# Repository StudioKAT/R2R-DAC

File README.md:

# R2R DAC

## 概要 / Overview

**R2R DAC** は、5つのゲート信号を階段状のコントロール電圧（CV）に変換する、2HPサイズのR-2RラダーDACモジュールです。
5つのゲート入力（/2, /4, /8, /16, /32）のON/OFFの組み合わせによって、0〜31段階のステップ電圧を生成する5ビットのデジタル→アナログ変換器として動作します。

クロックディバイダーやゲートシーケンサーと組み合わせることで、周期的な階段波、疑似ランダムなCVパターン、アルペジオ風のピッチ変化、フィルターやVCAのステップモジュレーションなどを簡単に作ることができます。
CV出力にはアッテネーターを備えており、ピッチCVからモジュレーション用途まで、パッチに合わせて出力レベルを調整できます。

**Update:** v2.0では、v1.0の4ビット仕様から5ビット仕様へ変更され、生成できるステップ数が16段階から32段階に拡張されました。

**R2R DAC** is a compact 2HP R-2R ladder DAC module that converts five gate signals into stepped control voltages (CV).
By combining the ON/OFF states of the five gate inputs (/2, /4, /8, /16, /32), it functions as a 5-bit digital-to-analog converter capable of generating 32 discrete voltage steps (0–31).

When paired with clock dividers or gate sequencers, it can create stepped waveforms, pseudo-random CV patterns, arpeggio-like pitch movement, or stepped modulation for filters, VCAs, and other CV destinations.
The CV output is equipped with an attenuator, allowing the output level to be adjusted for anything from pitch control to general modulation use.

**Update:** In v2.0, the design has been updated from the 4-bit configuration of v1.0 to a 5-bit R-2R DAC, expanding the available resolution from 16 steps to 32 steps.

## 仕様 / Spec
- Format: Eurorack
- Function: R2R DAC
- Current needs: +12V: 15mA, -12V: 15mA
- Width: 2 HP
- Depth: 28mm (including power connector)

## 販売 / Sales

StudioKATオフィシャルショップで販売しています。(日本国内限定)  
https://www.studiokat.jp/items/149564763

## ライセンス / License

この作品は [Creative Commons 表示 - 継承 4.0 国際 (CC BY-SA 4.0)](https://creativecommons.org/licenses/by-sa/4.0/deed.ja) の下でライセンスされています。  
This work is licensed under the [Creative Commons Attribution-ShareAlike 4.0 International License](https://creativecommons.org/licenses/by-sa/4.0/).

## クレジット / Credits

- Designed by : StudioKAT
- Website : https://www.studiokat.jp/
- GitHub : https://github.com/StudioKAT
- X(Twitter) : https://x.com/StudioKAT_synth
- Instagram : https://www.instagram.com/studiokat_modular/

## 更新履歴 / Changelog

- `2025-11-22` v1.0 Released version 1.0
- `2026-07-05` v2.0 Released version 2.0

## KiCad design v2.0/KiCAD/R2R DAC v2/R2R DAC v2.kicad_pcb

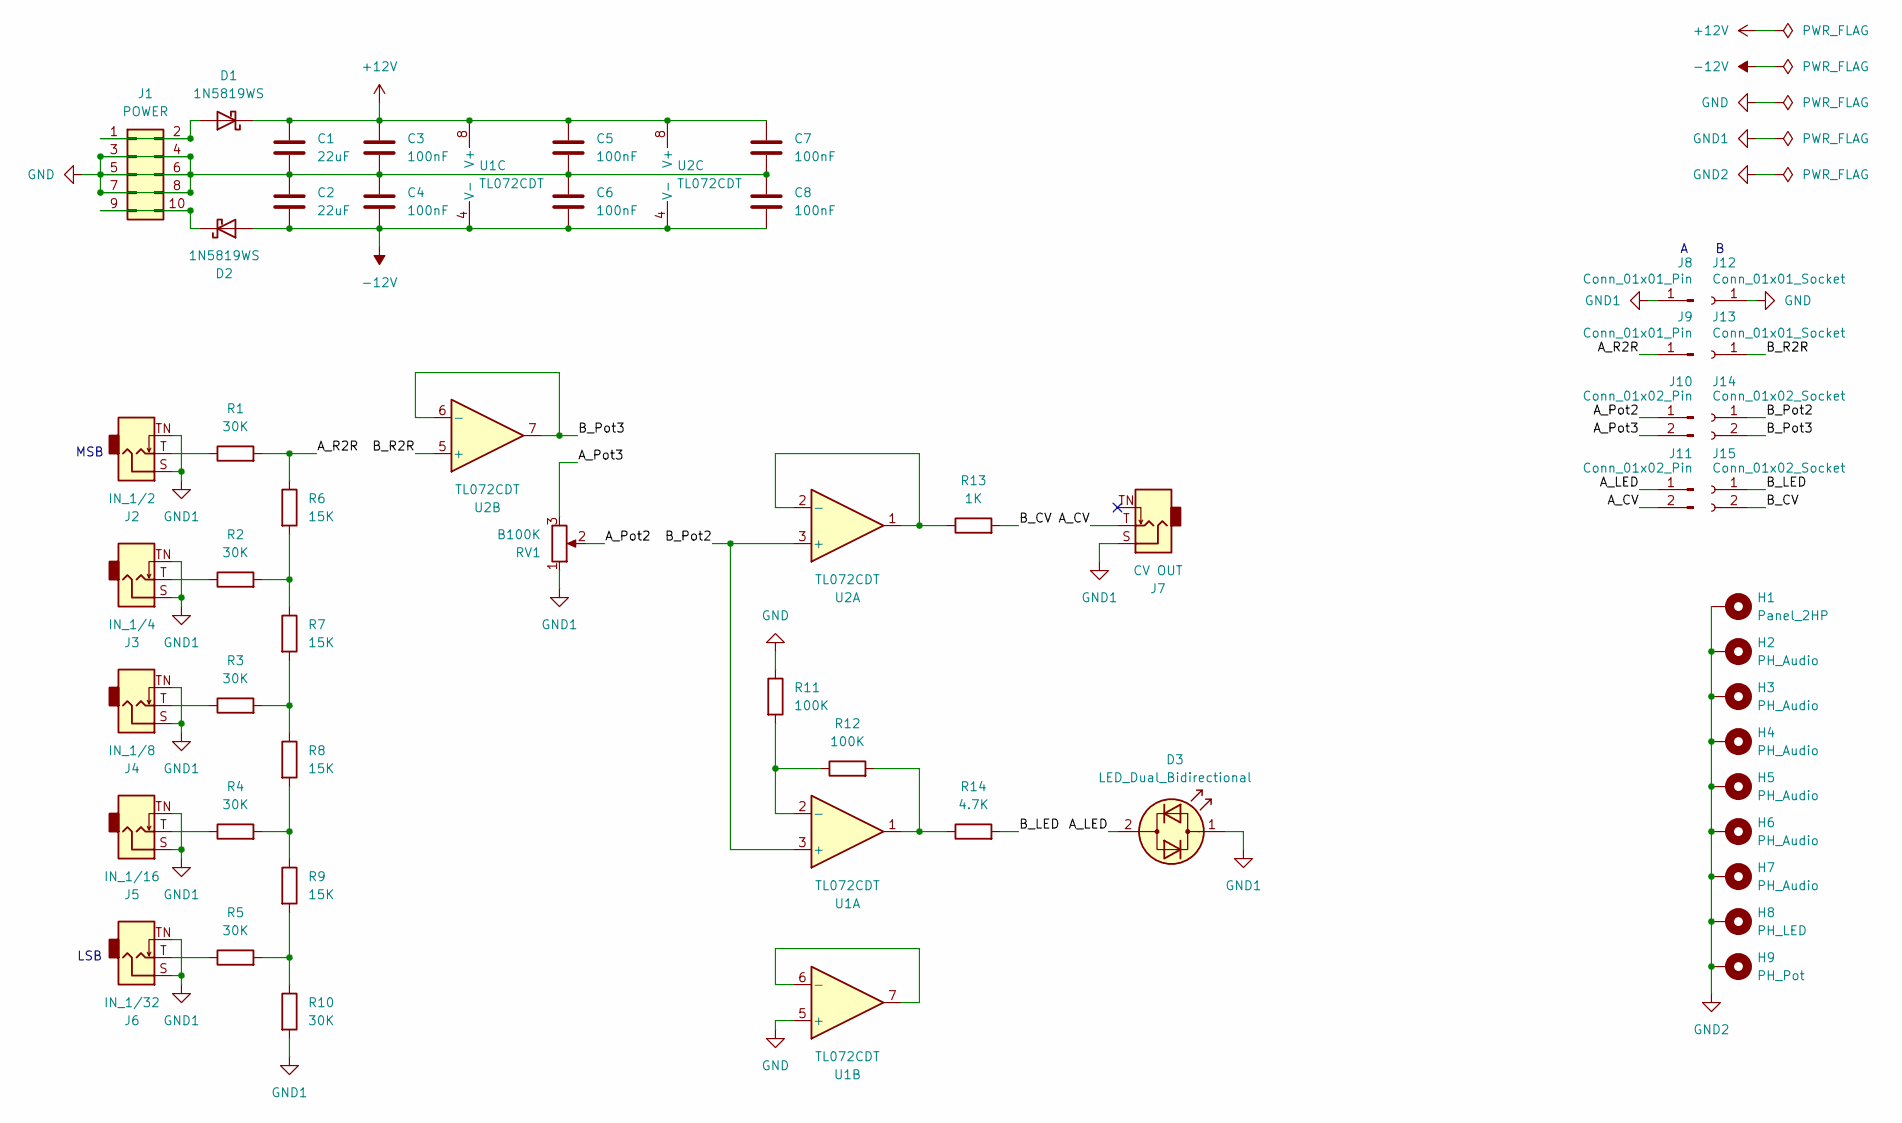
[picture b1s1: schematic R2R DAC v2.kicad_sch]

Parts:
C1, C2: 22uF; C_0805_2012Metric; LCSC C45783
C3, C4, C5, C6, C7, C8: 100nF; C_0603_1608Metric; LCSC C14663
D1, D2: 1N5819WS; D_SOD-323; LCSC C64886
D3: LED_Dual_Bidirectional; LED_D3.0mm_Clear
H1: Panel_2HP
H2, H3, H4, H5, H6, H7: PH_Audio; PH_AudioJack_3.5mm_Pad
H8: PH_LED; PH_LED_3.0mm_Pad
H9: PH_Pot; PH_RV09
J1: POWER; PinHeader_2x05_2.54mm_Europower
J2: IN_1/2; AudioJack_PJ301M-12
J3: IN_1/4; AudioJack_PJ301M-12
J4: IN_1/8; AudioJack_PJ301M-12
J5: IN_1/16; AudioJack_PJ301M-12
J6: IN_1/32; AudioJack_PJ301M-12
J7: CV OUT; AudioJack_PJ301M-12
J8, J9: Conn_01x01_Pin; PinHeader_1x01_P2.54mm_Vertical
J10, J11: Conn_01x02_Pin; PinHeader_1x02_P2.54mm_Vertical
J12, J13: Conn_01x01_Socket; PinSocket_1x01_P2.54mm_Vertical
J14, J15: Conn_01x02_Socket; PinSocket_1x02_P2.54mm_Vertical
R1, R2, R3, R4, R5, R10: 30K; R_0603_1608Metric; LCSC C22984
R6, R7, R8, R9: 15K; R_0603_1608Metric; LCSC C22809
R11, R12: 100K; R_0603_1608Metric; LCSC C25803
R13: 1K; R_0603_1608Metric; LCSC C21190
R14: 4.7K; R_0603_1608Metric; LCSC C23162
RV1: B100K; Potentiometer_RV09
U1, U2: TL072CDT; SOIC-8_3.9x4.9mm_P1.27mm; LCSC C6961

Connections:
+12V: C1.1, C3.1, C5.1, C7.1, D1.1 (K), U1.8 (V+), U2.8 (V+)
-12V: C2.2, C4.2, C6.2, C8.2, D2.2 (A), U1.4 (V-), U2.4 (V-)
/A_CV: J7.T, J11.2
/A_LED: D3.2 (AK), J11.1
/A_Pot2: J10.1, RV1.2
/A_Pot3: J10.2, RV1.3
/A_R2R: J9.1 (Pin_1_1), R1.2, R6.1
/B_CV: J15.2, R13.2
/B_LED: J15.1, R14.2
/B_Pot2: J14.1, U1.3 (+), U2.3 (+)
/B_Pot3: J14.2, U2.6 (-), U2.7
/B_R2R: J13.1 (Pin_1_1), U2.5 (+)
GND: C1.2, C2.1, C3.2, C4.1, C5.2, C6.1, C7.2, C8.1, J1.3, J1.4, J1.5, J1.6, J1.7, J1.8, J12.1 (Pin_1_1), R11.1, U1.5 (+)
GND1: D3.1 (KA), J2.S, J2.TN, J3.S, J3.TN, J4.S, J4.TN, J5.S, J5.TN, J6.S, J6.TN, J7.S, J8.1 (Pin_1_1), R10.2, RV1.1
GND2: H1.1 (1_1), H2.1 (1_1), H3.1 (1_1), H4.1 (1_1), H5.1 (1_1), H6.1 (1_1), H7.1 (1_1), H8.1 (1_1), H9.1 (1_1)
unnamed: D1.2 (A), J1.1, J1.2
unnamed: D2.1 (K), J1.9, J1.10
unnamed: J2.T, R1.1
unnamed: J3.T, R2.1
unnamed: J4.T, R3.1
unnamed: J5.T, R4.1
unnamed: J6.T, R5.1
unnamed: R2.2, R6.2, R7.1
unnamed: R3.2, R7.2, R8.1
unnamed: R4.2, R8.2, R9.1
unnamed: R5.2, R9.2, R10.1
unnamed: R12.2, R14.1, U1.1
unnamed: R11.2, R12.1, U1.2 (-)
unnamed: U1.6 (-), U1.7
unnamed: R13.1, U2.1, U2.2 (-)

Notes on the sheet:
MSB
A B
LSB

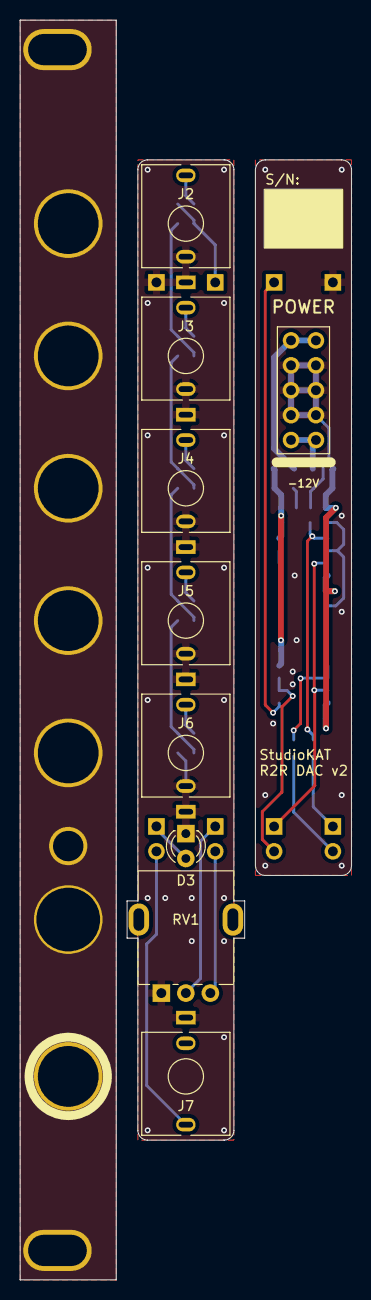
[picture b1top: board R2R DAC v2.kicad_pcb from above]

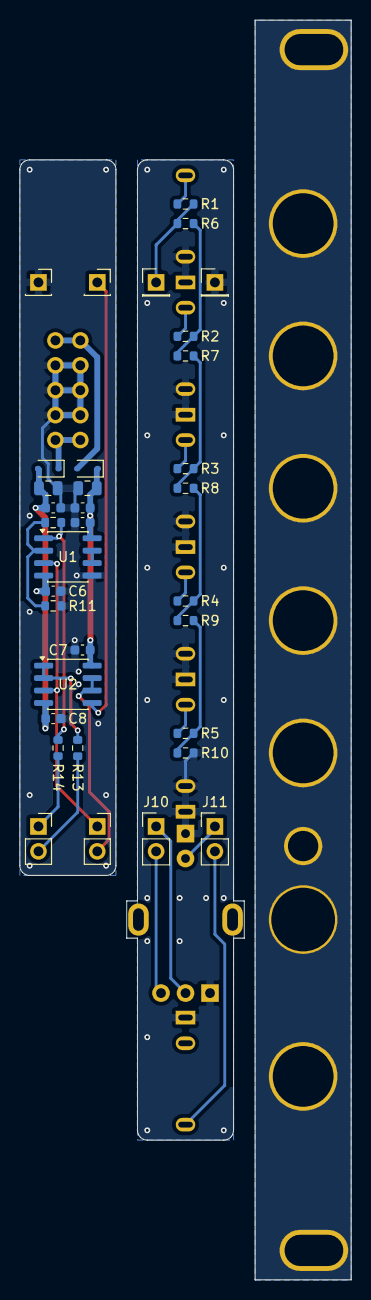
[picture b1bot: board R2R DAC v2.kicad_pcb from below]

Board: 2 copper layers, 33.8 x 128.5 mm, 52 parts (34 on the bottom side), 30 nets.

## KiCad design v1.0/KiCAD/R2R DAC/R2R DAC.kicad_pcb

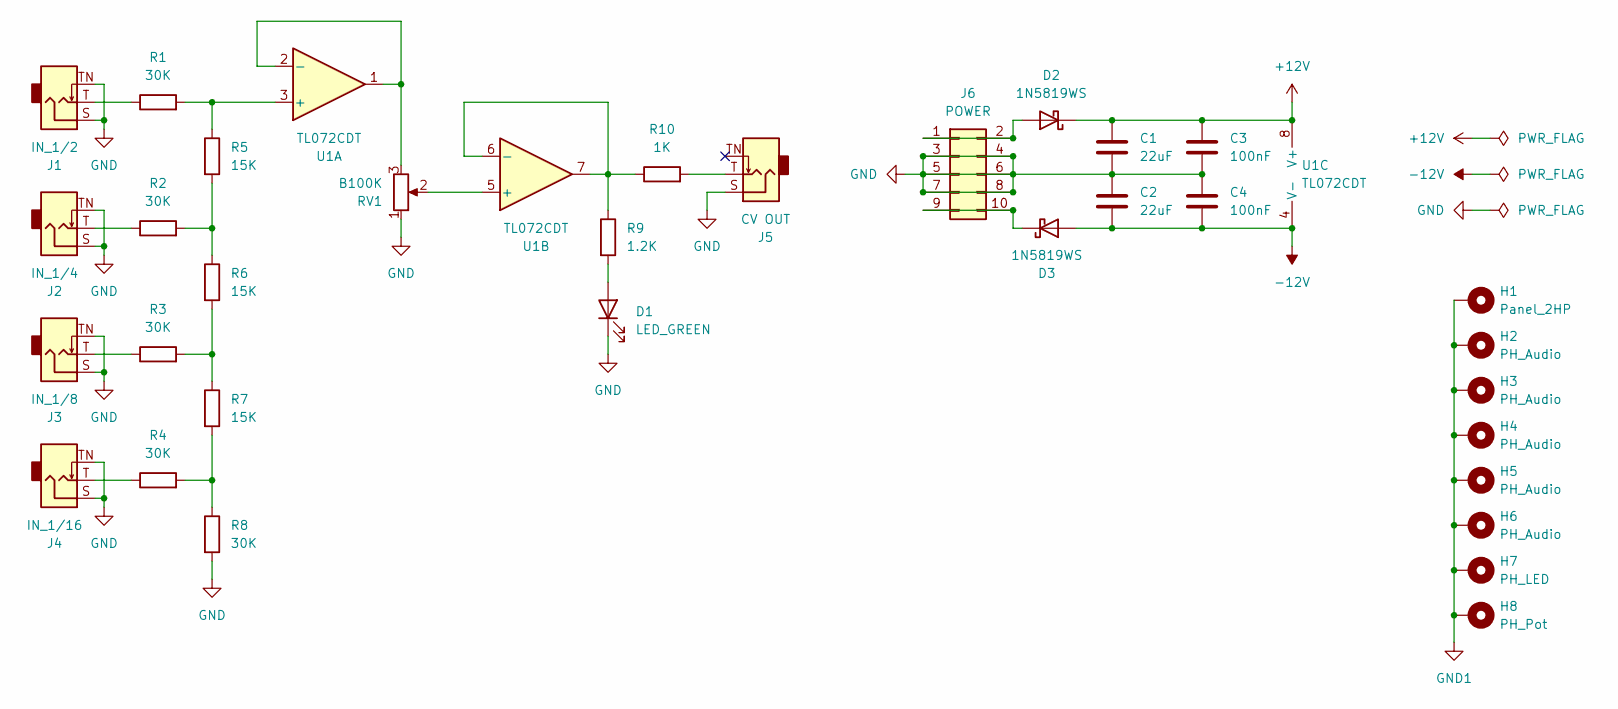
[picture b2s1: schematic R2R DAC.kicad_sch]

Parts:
C1, C2: 22uF; C_0805_2012Metric; LCSC C45783
C3, C4: 100nF; C_0603_1608Metric; LCSC C14663
D1: LED_GREEN; LED_D3.0mm_2hp
D2, D3: 1N5819WS; D_SOD-323; LCSC C64886
H1: Panel_2HP
H2, H3, H4, H5, H6: PH_Audio; PH_AudioJack_3.5mm_Pad
H7: PH_LED; PH_LED_3.0mm_Pad
H8: PH_Pot; PH_RV09
J1: IN_1/2; AudioJack_PJ301M-12
J2: IN_1/4; AudioJack_PJ301M-12
J3: IN_1/8; AudioJack_PJ301M-12
J4: IN_1/16; AudioJack_PJ301M-12
J5: CV OUT; AudioJack_PJ301M-12_2hp_R
J6: POWER; PinHeader_2x05_2.54mm_Europower
R1, R2, R3, R4, R8: 30K; R_0603_1608Metric; LCSC C22984
R5, R6, R7: 15K; R_0603_1608Metric; LCSC C22809
R9: 1.2K; R_0603_1608Metric; LCSC C22765
R10: 1K; R_0603_1608Metric; LCSC C21190
RV1: B100K; Potentiometer_RV09
U1: TL072CDT; SOIC-8_3.9x4.9mm_P1.27mm; LCSC C6961

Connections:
+12V: C1.1, C3.1, D2.1 (K), U1.8 (V+)
-12V: C2.2, C4.2, D3.2 (A), U1.4 (V-)
GND: C1.2, C2.1, C3.2, C4.1, D1.1 (K), J1.S, J1.TN, J2.S, J2.TN, J3.S, J3.TN, J4.S, J4.TN, J5.S, J6.3, J6.4, J6.5, J6.6, J6.7, J6.8, R8.2, RV1.1
GND1: H1.1, H2.1, H3.1, H4.1, H5.1, H6.1, H7.1, H8.1
unnamed: D1.2 (A), R9.2
unnamed: D2.2 (A), J6.1, J6.2
unnamed: D3.1 (K), J6.9, J6.10
unnamed: J1.T, R1.1
unnamed: J2.T, R2.1
unnamed: J3.T, R3.1
unnamed: J4.T, R4.1
unnamed: J5.T, R10.2
unnamed: R2.2, R5.2, R6.1
unnamed: R3.2, R6.2, R7.1
unnamed: R4.2, R7.2, R8.1
unnamed: R1.2, R5.1, U1.3 (+)
unnamed: RV1.3, U1.1, U1.2 (-)
unnamed: RV1.2, U1.5 (+)
unnamed: R9.1, R10.1, U1.6 (-), U1.7

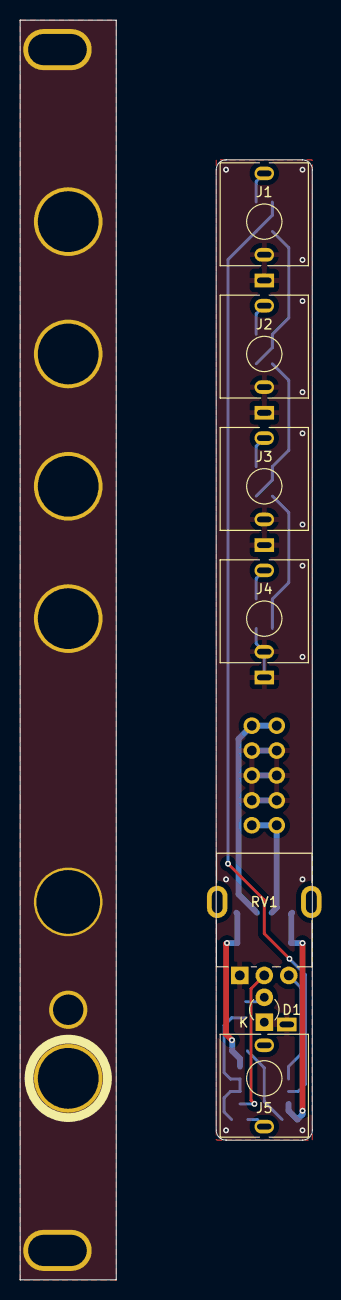
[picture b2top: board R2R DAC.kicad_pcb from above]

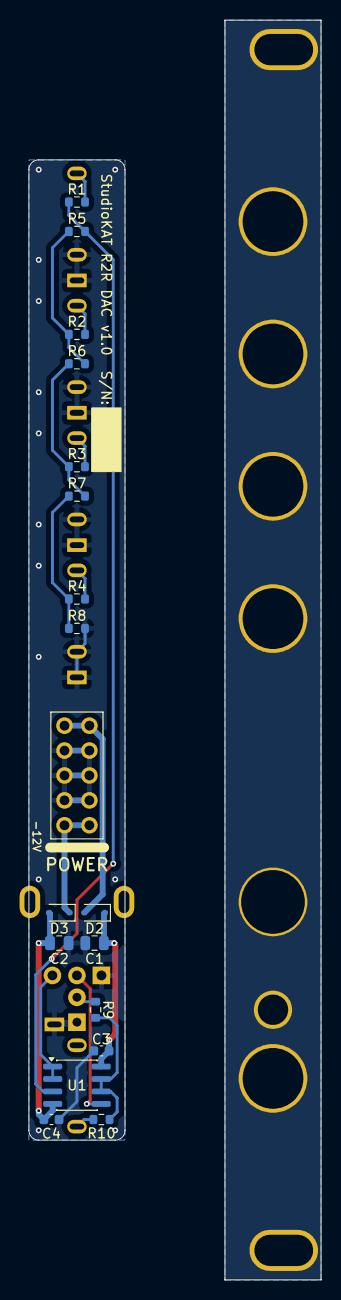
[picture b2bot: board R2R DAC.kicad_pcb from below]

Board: 2 copper layers, 29.8 x 128.5 mm, 33 parts (18 on the bottom side), 19 nets.
